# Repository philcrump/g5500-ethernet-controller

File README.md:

# G-5500 Ethernet Rotator Controller 

This project exists as firmware and a 'shield' board on an ST NUCLEO-STM32F429ZI Development Board.

The firmware exposes a web server on port 80, through which the rotator can be monitored and commanded.

This project is built on ChibiOS 17.6.x with LwIP 1.4.1

## Wiring

**J1** - "AZ FEEDBACK"
1. G-5500 Azimuth Pin 1 (Feedback Rheostat 360-end)
2. G-5500 Azimuth Pin 2 (Feedback Rheostat Wiper)
3. G-5500 Azimuth Pin 3 (Feedback Rheostat 0-end)

**J6** - "AZIMUTH" -> "MOTOR"
1. (L) G-5500 Azimuth Pin 4 (Motor Winding 1)
2. (R) G-5500 Azimuth Pin 5 (Motor Winding 2)
3. (C) G-5500 Azimuth Pin 6 (Motor Center Tap)

## TODO

- [x] Flash Storage of settings (on settings branch)
- [ ] Interface to edit presets

### Possible future features

- [ ] Merge in satellite tracking computations from old project (using NTP, GPS, & libpredict)
- [ ] Update to ChibiOS 18.2.x (There seems to be a DHCP Client bug - needs investigation)

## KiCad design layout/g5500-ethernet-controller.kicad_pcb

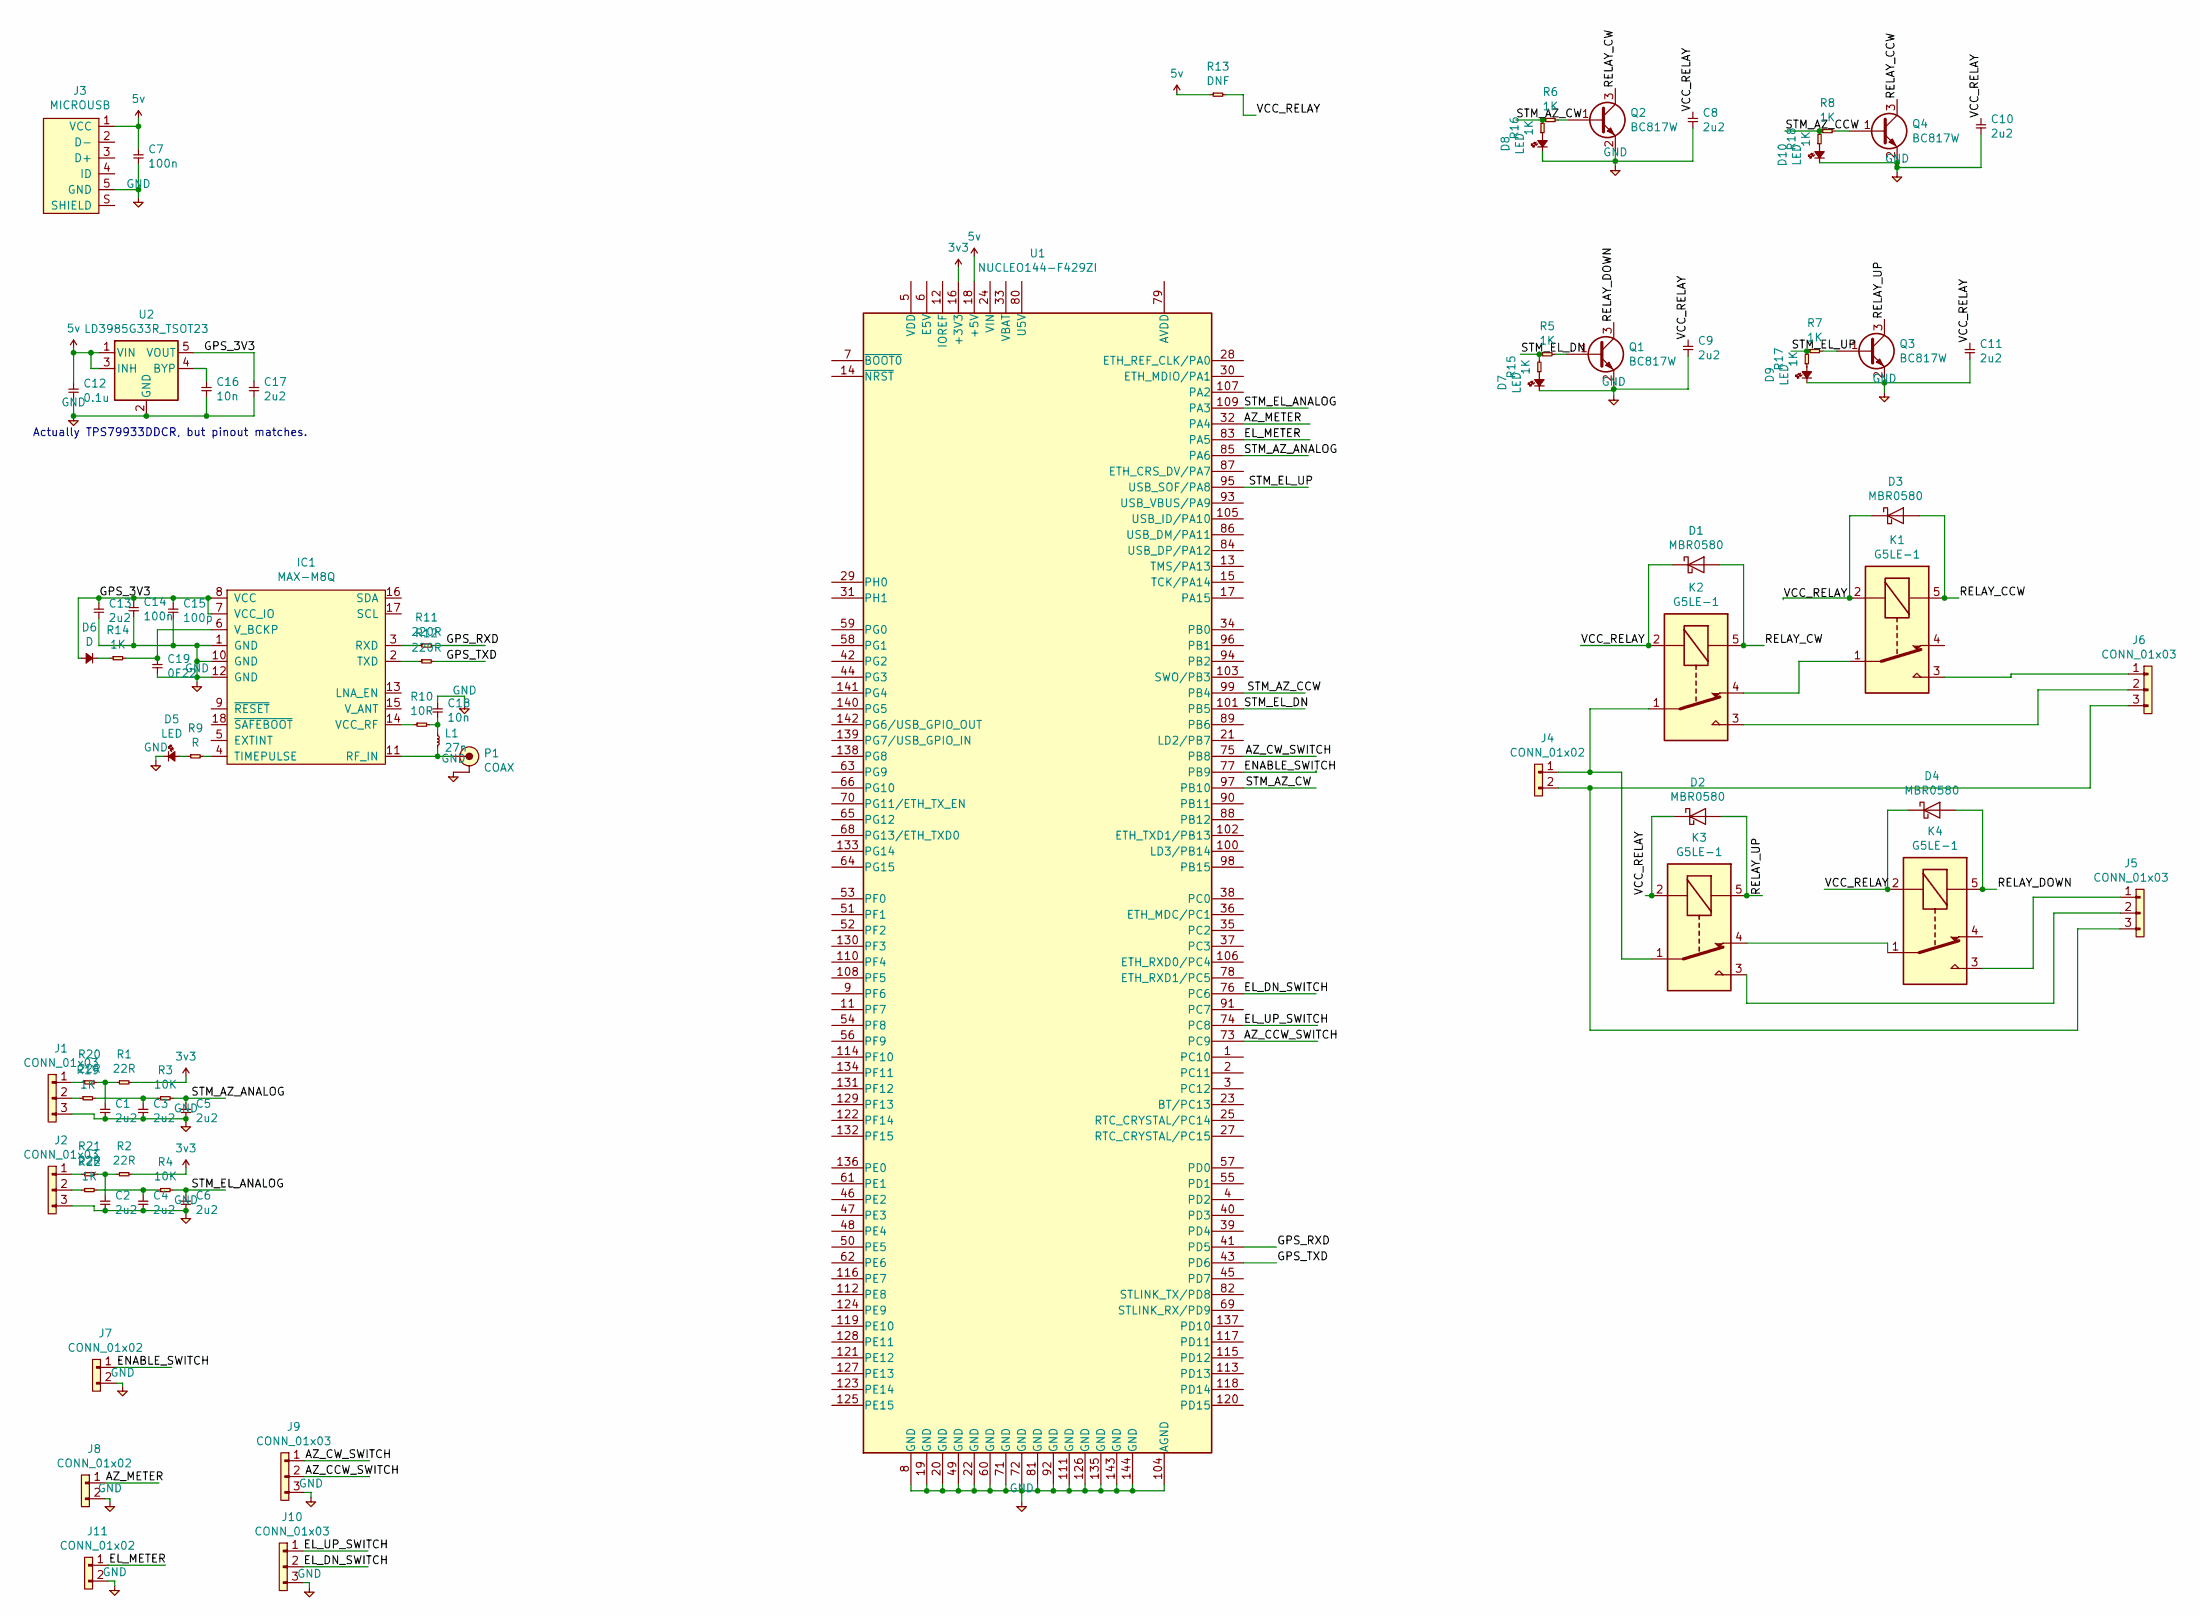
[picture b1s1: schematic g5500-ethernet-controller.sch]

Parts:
C1, C2, C3, C4, C5, C6, C8, C9, C10, C11, C13, C17: 2u2; 0603
C7, C14: 100n; 0603
C12: 0.1u; 0603
C15: 100p; 0603
C16, C18: 10n; 0402
C19: 0F22; C_Rect_L11.5mm_W9.8mm_P10.00mm_MKT; Farnell_OC 9692690
D1, D2, D3, D4: MBR0580; D_SOD-123
D5, D7, D8, D9, D10: LED; 0603-LED
D6: D; D_SOD-123
IC1: MAX-M8Q
J1, J2, J5, J6, J9, J10: CONN_01x03; Molex_KK-254_AE-6410-03A_1x03_P2.54mm_Vertical
J3: MICROUSB; MICROUSB_MOLEX_47589-0001; Farnell 1568023
J4, J7, J8, J11: CONN_01x02; Molex_KK-254_AE-6410-02A_1x02_P2.54mm_Vertical
K1, K2, K3, K4: G5LE-1; Relay_SPDT_OMRON-G5LE-1
L1: 27n; 0402
P1: COAX; SMA-EDGE; Farnell 1608592
Q1, Q2, Q3, Q4: BC817W; SOT-323_SC-70
R1, R2, R20, R21: 22R; 0603
R3, R4: 10K; 0603
R5, R6, R7, R8, R14, R15, R16, R17, R18, R19, R22: 1K; 0603
R9: R; 0603
R10: 10R; 0402
R11, R12: 220R; 0603
R13: DNF; 0603
U1: NUCLEO144-F429ZI; ST_Morpho_Connector_144_STLink
U2: LD3985G33R_TSOT23; TSOT-23-5

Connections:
3v3: R1.2, R2.2, U1.16 (+3V3)
5v: C7.1, C12.1, J3.1 (VCC), R13.1, U1.18 (+5V), U2.1 (VIN), U2.3 (INH)
/AZ_CCW_SWITCH: J9.2, U1.73 (PC9)
/AZ_CW_SWITCH: J9.1, U1.75 (PB8)
/AZ_METER: J8.1, U1.32 (PA4)
/EL_DN_SWITCH: J10.2, U1.76 (PC6)
/EL_METER: J11.1, U1.83 (PA5)
/EL_UP_SWITCH: J10.1, U1.74 (PC8)
/ENABLE_SWITCH: J7.1, U1.77 (PB9)
/GPS_3V3: C13.1, C14.1, C15.1, C17.1, D6.2, IC1.7 (VCC_IO), IC1.8 (VCC), U2.5 (VOUT)
/GPS_RXD: R11.2, U1.41 (PD5)
/GPS_TXD: R12.2, U1.43 (PD6)
/RELAY_CCW: D3.2 (A), K1.5, Q4.3 (C)
/RELAY_CW: D1.2 (A), K2.5, Q2.3 (C)
/RELAY_DOWN: D4.2 (A), K4.5, Q1.3 (C)
/RELAY_UP: D2.2 (A), K3.5, Q3.3 (C)
/STM_AZ_ANALOG: C5.1, R3.2, U1.85 (PA6)
/STM_AZ_CCW: R8.1, R18.2, U1.99 (PB4)
/STM_AZ_CW: R6.1, R16.2, U1.97 (PB10)
/STM_EL_ANALOG: C6.1, R4.2, U1.109 (PA3)
/STM_EL_DN: R5.1, R15.2, U1.101 (PB5)
/STM_EL_UP: R7.1, R17.2, U1.95 (USB_SOF/PA8)
/VCC_RELAY: C8.1, C9.1, C10.1, C11.1, D1.1 (K), D2.1 (K), D3.1 (K), D4.1 (K), K1.2, K2.2, K3.2, K4.2, R13.2
GND: C1.2, C2.2, C3.2, C4.2, C5.2, C6.2, C7.2, C8.2, C9.2, C10.2, C11.2, C12.2, C13.2, C14.2, C15.2, C16.2, C17.2, C18.1, C19.2, D5.1, D7.1, D8.1, D9.1, D10.1, IC1.1 (GND), IC1.10 (GND), IC1.12 (GND), J1.3, J2.3, J3.5 (GND), J7.2, J8.2, J9.3, J10.3, J11.2, P1.2 (GND), Q1.2 (E), Q2.2 (E), Q3.2 (E), Q4.2 (E), U1.8 (GND), U1.19 (GND), U1.20 (GND), U1.22 (GND), U1.49 (GND), U1.60 (GND), U1.71 (GND), U1.72 (GND), U1.81 (GND), U1.92 (GND), U1.104 (AGND), U1.111 (GND), U1.126 (GND), U1.135 (GND), U1.143 (GND), U1.144 (GND), U2.2 (GND)
unnamed: C1.1, R1.1, R20.2
unnamed: C2.1, R2.1, R21.2
unnamed: C3.1, R3.1, R19.2
unnamed: C4.1, R4.1, R22.2
unnamed: C16.1, U2.4 (BYP)
unnamed: C18.2, L1.1, R10.2
unnamed: C19.1, IC1.6 (V_BCKP), R14.2
unnamed: D5.2, R9.1
unnamed: D6.1, R14.1
unnamed: D7.2, R15.1
unnamed: D8.2, R16.1
unnamed: D9.2, R17.1
unnamed: D10.2, R18.1
unnamed: IC1.2 (TXD), R12.1
unnamed: IC1.3 (RXD), R11.1
unnamed: IC1.4 (TIMEPULSE), R9.2
unnamed: IC1.11 (RF_IN), L1.2, P1.1 (RF)
unnamed: IC1.14 (VCC_RF), R10.1
unnamed: J1.1, R20.1
unnamed: J1.2, R19.1
unnamed: J2.1, R21.1
unnamed: J2.2, R22.1
unnamed: J4.1, K2.1, K3.1
unnamed: J4.2, J5.3, J6.3
unnamed: J5.1, K4.3
unnamed: J5.2, K3.3
unnamed: J6.1, K1.3
unnamed: J6.2, K2.3
unnamed: K1.1, K2.4
unnamed: K3.4, K4.1
unnamed: Q1.1 (B), R5.2
unnamed: Q2.1 (B), R6.2
unnamed: Q3.1 (B), R7.2
unnamed: Q4.1 (B), R8.2

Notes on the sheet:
Actually TPS79933DDCR, but pinout matches.

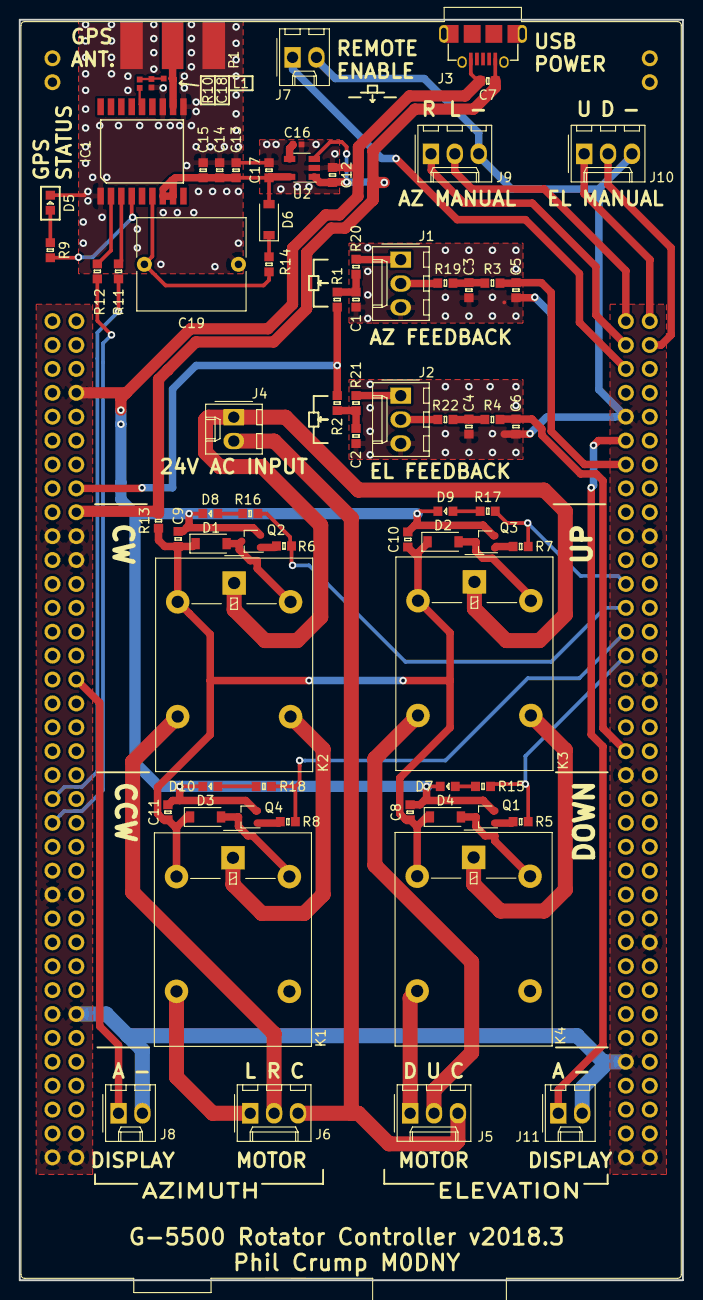
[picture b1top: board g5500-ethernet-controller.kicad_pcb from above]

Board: 2 copper layers, 70.5 x 134.0 mm, 75 parts (0 on the bottom side), 58 nets.

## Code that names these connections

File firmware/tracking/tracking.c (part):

#include "../main.h"

/* AZ - PA6 - ADC123_IN6 - using ADC1 */
/* EL - PA3 - ADC12_IN3 - using ADC1 */

/* AZ CW  - PB10 */
/* AZ CCW - PB4 */
/* EL UP  - PA8 */
/* EL DN  - PB5 */

#define TRACKING_AZ_CW(state)   if(state) { palSetPad(GPIOB, 10); } else { palClearPad(GPIOB, 10); }
#define TRACKING_AZ_CCW(state)  if(state) { palSetPad(GPIOB,  4); } else { palClearPad(GPIOB,  4); }
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
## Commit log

2018-02-11 Initial commit.
2018-02-11 firmware/compile: First-run fixes.
2018-02-19 Layout: Add start of work.
2018-02-20 layout: Schematic poking, drag in components used in etherswitch.
2018-03-25 Progress on layout.
2018-03-26 Layout nearly done.
2018-04-02 layout: Finish and send off v1.
2018-09-23 Update source tree.
2018-09-24 Track fw work.
2018-09-24 Add travis CI.
2018-09-24 Add README.
2018-09-24 travis: Install p7zip.
2018-09-24 travis: Install p7zip-full.
2018-09-24 layout: Add BOM.
2018-09-24 firmware: Misc improvements.
2018-10-02 Update chibios ref.
2018-10-08 Firmware progress.
2018-10-08 Fix Travis build (add WEBPASSWORD).
2018-10-08 Minor web fixes.
2018-10-10 firmware and web tweaks.
2018-10-31 Web updates.
2018-10-31 Revert ChibiOS to 17.6.x
2018-10-31 Fixi build for 17.6 (not run).
2018-12-02 Update Chibi Ref.
2018-12-02 Mutex on tracking state, misc fixes and tweaks.
2018-12-02 WIP flash-stored settings.
2018-12-02 Add content to README.
2018-12-02 README.md: Tweaks.
2018-12-02 README.md: Tweak image layout.
2019-09-19 firmware/web/: Handle iOS HTTP request fragmentation (fixes mobile/iOS connection starvation issue).
2019-09-19 firmware/ChibiOS: Update upstream ref.
2019-09-19 web/web.c: Fix buffer append.
2019-09-21 firmware/openocd.cfg: Add OpenOCD config.
2019-09-21 firmware/web/src/index.html: Put year on copyright.
2019-09-21 firmware/web/src/index.js: JS improvements.
2022-03-12 web/index.html: Update bearing presets.
2022-03-12 web/index.html: Update copyright year.
2022-03-12 firmware/tracking: Put in calibration values for newer G-5500 (tested).
